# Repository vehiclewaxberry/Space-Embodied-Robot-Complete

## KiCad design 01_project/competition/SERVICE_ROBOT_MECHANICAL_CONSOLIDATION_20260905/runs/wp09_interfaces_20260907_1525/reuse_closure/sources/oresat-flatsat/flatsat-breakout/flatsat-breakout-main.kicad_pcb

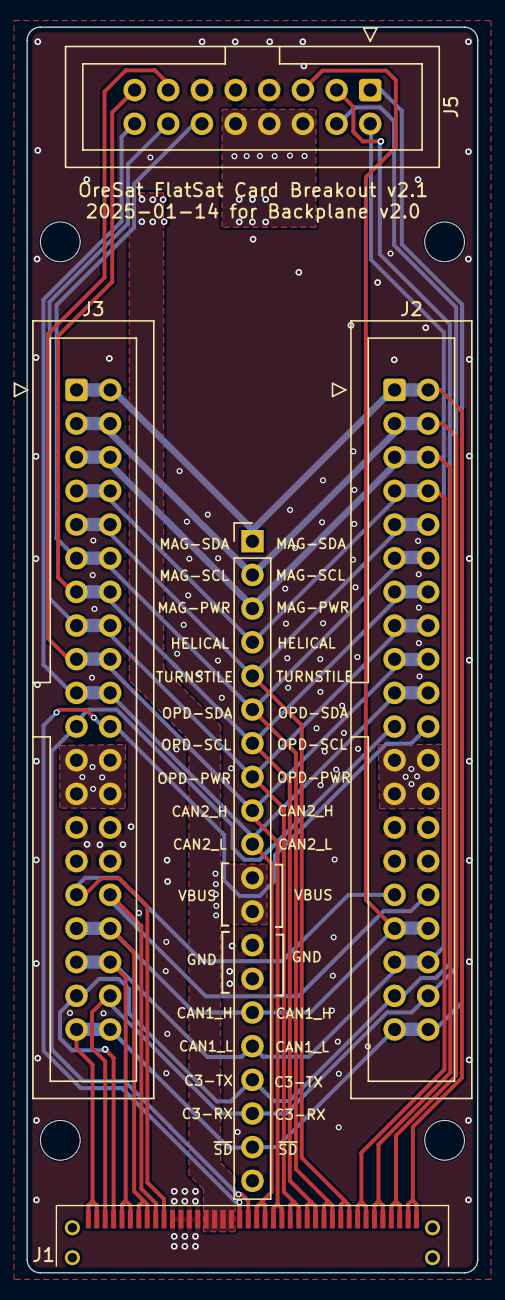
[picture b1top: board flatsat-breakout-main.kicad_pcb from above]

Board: 4 copper layers, 34.0 x 94.0 mm, 5 parts (0 on the bottom side), 21 nets.

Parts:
J1: SFM-120-02-L-DH-TR; SFM-120-02-X-DH
J2, J3: 61204021621; IDC-Header_2x20_P2.54mm_Vertical
J4: 68000-227HLF; PinHeader_1x20_P2.54mm_Vertical
J5: Conn_02x08_Odd_Even; IDC-Header_2x08_P2.54mm_Vertical

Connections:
/HELICAL-DEPLOY: J1.7, J1.8, J2.7, J2.8, J3.7, J3.8, J4.4
/MAG-POWER: J1.5, J1.6, J2.5, J2.6, J3.5, J3.6, J4.3
/MAG-SCL: J1.3, J1.4, J2.3, J2.4, J3.3, J3.4, J4.2
/MAG-SDA: J1.1, J1.2, J2.1, J2.2, J3.1, J3.2, J4.1
/SPARE21: J1.21, J2.21, J3.21
/SPARE22: J1.22, J2.22, J3.22
/SPARE31: J1.31, J2.31, J3.31
/SPARE32: J1.32, J2.32, J3.32
/TURNSTILE-DEPLOY: J1.9, J1.10, J2.9, J2.10, J3.9, J3.10, J4.5
C3-UART-RX: J1.38, J2.38, J3.38, J4.18, J5.4
C3-UART-TX: J1.37, J2.37, J3.37, J4.17, J5.3
CAN1_H: J1.33, J1.34, J2.33, J2.34, J3.33, J3.34, J4.15, J5.5
CAN1_L: J1.35, J1.36, J2.35, J2.36, J3.35, J3.36, J4.16, J5.2
CAN2_H: J1.17, J1.18, J2.17, J2.18, J3.17, J3.18, J4.9, J5.13
CAN2_L: J1.19, J1.20, J2.19, J2.20, J3.19, J3.20, J4.10, J5.16
GND: J1.27, J1.28, J1.29, J1.30, J2.27, J2.28, J2.29, J2.30, J3.27, J3.28, J3.29, J3.30, J4.13, J4.14, J4.20, J5.7, J5.9, J5.11
OPD_PWR: J1.15, J1.16, J2.15, J2.16, J3.15, J3.16, J4.8, J5.14
OPD_SCL: J1.13, J1.14, J2.13, J2.14, J3.13, J3.14, J4.7, J5.15
OPD_SDA: J1.11, J1.12, J2.11, J2.12, J3.11, J3.12, J4.6, J5.12
VBUS: J1.23, J1.24, J1.25, J1.26, J2.23, J2.24, J2.25, J2.26, J3.23, J3.24, J3.25, J3.26, J4.11, J4.12, J5.6, J5.8, J5.10
~SD: J1.39, J1.40, J2.39, J2.40, J3.39, J3.40, J4.19, J5.1

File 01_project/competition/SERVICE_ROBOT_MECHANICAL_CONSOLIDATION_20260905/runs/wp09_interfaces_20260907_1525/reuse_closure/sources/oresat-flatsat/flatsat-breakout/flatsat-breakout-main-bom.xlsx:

OreSat FlatSat Card Breakout Board v2.0
Qty | P/NP | Parts | MFR | MPN | Description | Generic | Module | Stock | DIST | DPN | DIST2 | DPN2 | Notes
1 | P | J1 | Samtec Inc. | SFM-120-02-L-DH-TR | 40 Position Receptacle Connector 0.050" (1.27mm) Surface Mount, Right Angle Gold | N | - | 0 | Digi-Key | SAM14509CT-ND |  |  | R/A version of backplane connector (NOT CARD CONNECTOR!)
2 | P | J2, J3 | Würth Elektronik | 61204021621 | Connector Header Through Hole 40 position 0.100" (2.54mm) Shrouded | Y | - | 0 | Digi-Key | 732-5401-ND |  |  | 20x2 shrouded 0.1" connector for IDC cable
1 | P | J4 | Amphenol ICC (FCI) | 68000-227HLF | Connector Header Through Hole 27 position 0.100" (2.54mm) | Y | - | 0 | Digi-Key | 68000-227HLF-ND |  |  | 27x1 0.1" header for getting at backplane signals
1 | P | J5 | Würth Elektronik | 61201621621 | CONN HEADER VERT 16POS 2.54MM | Y | - | 0 | Digi-Key | 732-2095-ND |  |  | Connector for OreSat backplane debug cable
 |  |  | Date | Notes
 |  |  | 45202 | Updated descriptions, added usual columns, added notes.

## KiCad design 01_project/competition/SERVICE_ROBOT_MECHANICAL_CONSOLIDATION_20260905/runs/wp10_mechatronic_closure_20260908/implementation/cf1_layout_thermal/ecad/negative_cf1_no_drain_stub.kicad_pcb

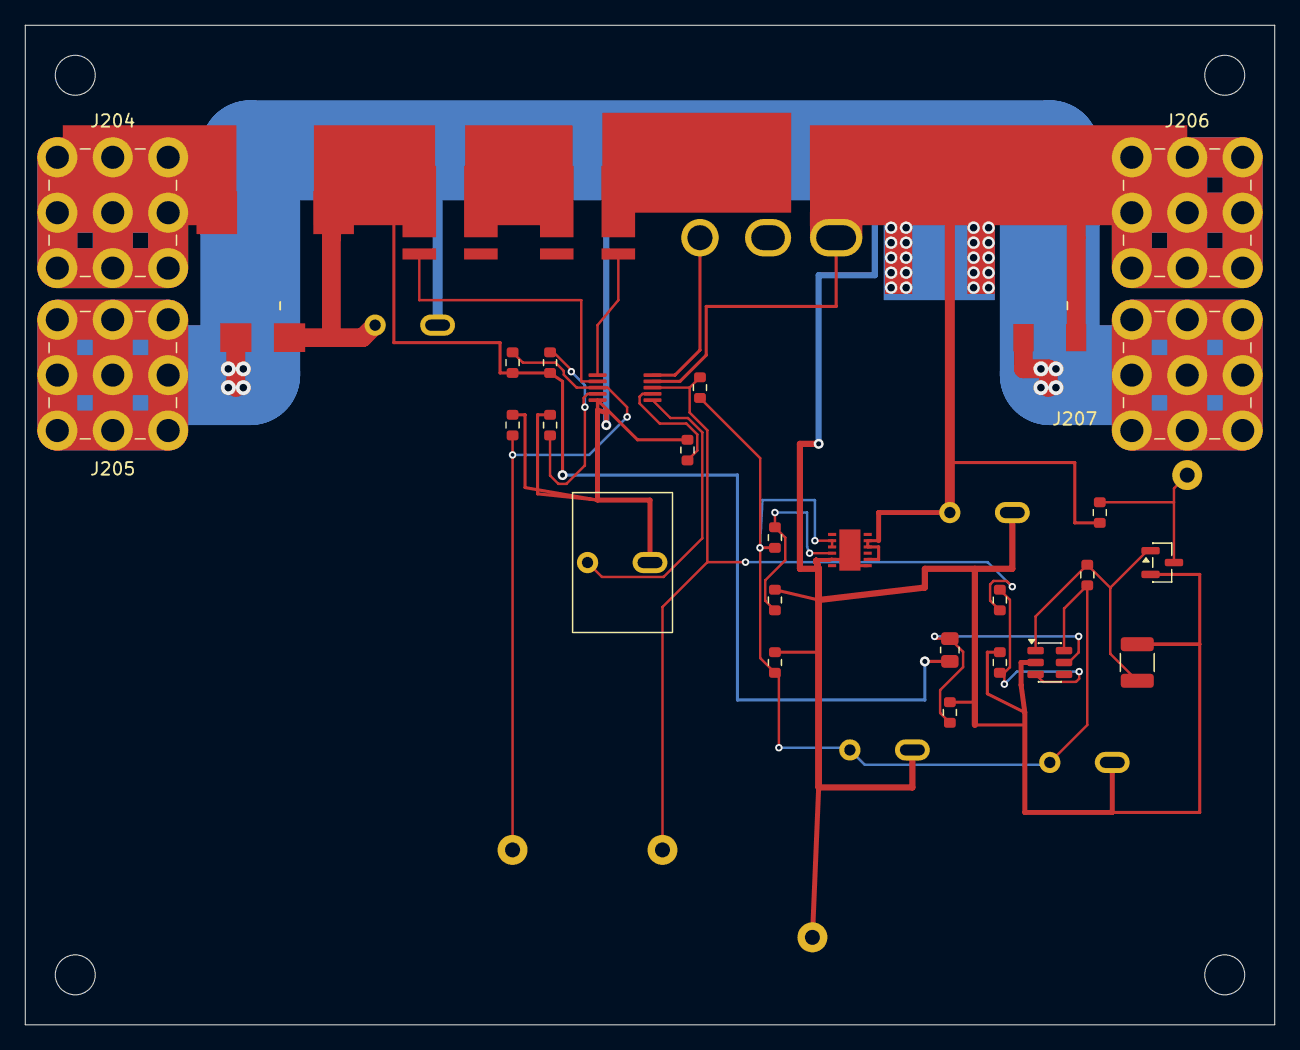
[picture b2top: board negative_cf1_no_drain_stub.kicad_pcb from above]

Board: 2 copper layers, 100.0 x 80.0 mm, 43 parts (0 on the bottom side), 18 nets.

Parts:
C201: MKP2C041001N00JSSD; C201_MKP2_1uF_P5_Slot2
C202, C213: MKP2D031001F00JSSD; MKP2_D031001F00_P5_Slot2
C211: MKS2D041501M00JSSD; MKS2_D041501M00_P5_Slot2
C212: MKS2D044701O00JSSD; MKS2_D044701O00_P5_Slot2
D201: SMBJ30A-13-F; SMBJ30A_A1K2
D202: STPS3H100U; STPS3H100U_A1K2
F201: 1025HC30-RTR; Fuse_Eaton_1025HC_20to30A_3p25x3p43_P9p35
J204, J205, J206, J207: 74651195R; MP_Wurth_WP-THRSH_74651195R
MH1, MH2, MH3, MH4: (no value)
PORT_ENABLE: PROJECT_WIRE_LANDING_NOT_OEM_CONNECTOR
PORT_PGD: PROJECT_WIRE_LANDING_NOT_OEM_CONNECTOR
PORT_RESET: PROJECT_WIRE_LANDING_NOT_OEM_CONNECTOR
PORT_SIGNAL_RETURN: PROJECT_WIRE_LANDING_NOT_OEM_CONNECTOR
Q201: IXTH75N10L2; IXTH_TO247_G1D2S3_P5p45_Slots
Q204: 2N7002K-7; SOT-23
R201: WSLP27262L000FEA; WSLP2726_KelvinSplit_TwoTerminals
R202: WSLP2726L2000FEA; WSLP2726_KelvinSplit_TwoTerminals
R203: TNPW060347K5BEEA; R_0603_1608Metric
R204: TNPW06035K90BEEA; R_0603_1608Metric
R205: TNPW0603120KBEEA; R_0603_1608Metric
R206, R212, R216: TNPW060310K0BEEA; R_0603_1608Metric
R207: TNPW060330K1BEEA; R_0603_1608Metric
R211: TNPW060338K3BEEA; R_0603_1608Metric
R213: TNPW06034K70FEEA; R_0603_1608Metric
R214: TNPW06033K48BEEA; R_0603_1608Metric
R215: TNPW0805374KBEEA; R_0805_2012Metric
R217: TNPW060333K0FEEA; R_0603_1608Metric
R218: TNPW12102M20FEEA; R_1210_3225Metric
R219: TNPW0603100KFEEA; R_0603_1608Metric
R220: TNPW060310K0FEEA; R_0603_1608Metric
R221: TNPW0603100RFEEA; R_0603_1608Metric
U201: LM5069MM-1; LM5069_DGS10_P0p5_NoEP
U205: LT3013EDE#PBF; LT3013_DE12_EP13_3x4_Pin1LeftTop
U206: TPS3808G01DBVR; SOT-23-6

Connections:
WP10_BAT_PROTECTED_PLUS: F201.1, J204.1
WP10_CHB_ENABLE: PORT_ENABLE.1, Q204.3, R219.2
WP10_CHB_ENABLE_GATE: Q204.1, R217.2, R218.1, U206.1
WP10_HS_OVLO: R205.2, R206.1, U201.4
WP10_HS_PGD: PORT_PGD.1, R214.2, R221.1, U201.8
WP10_HS_POWER_LIMIT: R207.1, U201.7
WP10_HS_TIMER: C201.1, U201.6
WP10_HS_UVLO: PORT_RESET.1, R203.2, R204.1, U201.3
WP10_INPUT_RETURN: C201.2, C202.2, C211.2, C212.2, C213.2, D201.1, D202.1, J205.1, J207.1, PORT_SIGNAL_RETURN.1, Q204.2, R204.2, R206.2, R207.2, R212.2, R213.2, R216.2, R218.2, R220.2, U201.5, U205.5, U205.7, U205.13, U206.2
WP10_MAIN_FUSED: C202.1, D201.2, F201.2, R201.1, R203.1, R205.1, R215.1, U201.2
WP10_MAIN_GATE: Q201.1, U201.10
WP10_MAIN_SENSE: Q201.2, R202.2, U201.1
WP10_PRECHARGED_PLUS: C211.1, D202.2, J206.1, Q201.3, R219.1, U201.9, U205.8, U205.10, U205.11
WP10_SENSE_MID: R201.2, R202.1
WP10_STARTUP_ADJ: R211.2, R212.1, U205.4
WP10_STARTUP_BIAS: C212.1, C213.1, R211.1, R213.1, R214.1, R217.1, U205.2, U205.3, U206.6
WP10_STARTUP_INPUT_SENSE: R215.2, R216.1, U206.5
WP10_STARTUP_PG_RECEIVER: R220.1, R221.2, U206.3
